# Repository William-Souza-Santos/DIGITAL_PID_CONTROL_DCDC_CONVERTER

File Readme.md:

# ⚡ FUZZY CONTROL APPLIED TO A BIDIRECTIONAL BUCK-BOOST DC-DC CONVERTER

This project presents the design and implementation of a four-switch bidirectional buck-boost DC-DC converter, featuring a fuzzy logic-based digital control system. The converter is designed for embedded and automotive power applications, ensuring stability, precision, and adaptability in bidirectional energy management.

---

## 🔍 Circuit Overview

---

## 🔧 Project Highlights

- Implementation of a non-linear fuzzy logic controller to dynamically regulate the converter's duty cycle.
- Simulations conducted in **MATLAB/Simulink** and **Proteus**, covering both open-loop and closed-loop control strategies.
- Embedded firmware developed for the **ATmega328P** microcontroller to enable real-time control.
- Complete **PCB design**, including schematic capture, PCB layout, and 3D visualization.

---

## 🎯 Objective

To design and validate a high-efficiency bidirectional DC-DC converter capable of operating in buck, boost, and buck-boost modes, maintaining stable output voltage under varying load and input conditions.

---

## 🚗 Motivation: Automotive and Beyond

The primary motivation for this project lies in the growing demand for reliable DC-DC power converters in **automotive systems**, where multiple ECUs operate at different voltage levels. A bidirectional buck-boost converter ensures safe and efficient energy flow between these modules and energy storage systems such as batteries or supercapacitors.

Although tailored for automotive use, the converter is also applicable to:

- 🔋 Battery Management Systems (BMS)  
- ☀️ Renewable Energy Systems  
- 🏭 Industrial Automation  
- ✈️ Aerospace Power Electronics  

---

## 🧪 Simulation: Circuit in Proteus

---

## 📝 Theoretical Foundations

<p align="center">
  <strong>Operating Modes</strong><br>
  <br>
</p>

<p align="center">
  <strong>BUCK</strong><br>
  <br>
</p>

<p align="center">
  <strong>BUCK-BOOST (Transition Mode)</strong><br>
  <br>
</p>

<p align="center">
  <strong>BOOST</strong><br>
  <br>
</p>

---

## 📝 Theoretical Foundations (Table Operating)

<p align="center">
  <strong>A-B OPERATING</strong><br>
  <br>
</p>

<p align="center">
  <strong>B-A OPERATING</strong><br>
  <br>
</p>

---

## 🔁 Bidirectional Operation (Open-Loop Tests)

<p align="center">
  <strong>A → B (Boost Mode)</strong><br>
  <br>
</p>

<p align="center">
  <strong>A → B (Buck Mode)</strong><br>
  <br>
</p>

<p align="center">
  <strong>B → A (Boost Mode)</strong><br>
  <br>
</p>

<p align="center">
  <strong>B → A (Buck Mode)</strong><br>
  <br>
</p>

<!--
## 📉 Theorical Fundamentation and Transition Mode

<p align="center">
  <strong>Buck Waveform</strong><br>
  <br>
</p>

<p align="center">
   <strong>Boost Waveform</strong><br>
  
</p>
-->

---
## 🖥️ Choosing a Microcontroller

<p align="center">
  <br>
</p>

---

## 🤖 Fuzzy Control System (Closed-Loop in Simulink)

<p align="center">
  <strong>Closed-Loop Control Model</strong><br>
  <br>
</p>

---

## 🧩 Schematic

<p align="center">
  <br>
</p>

---

## 🧱 3D PCB View

<p align="center">
  <br>
</p>

---

## 👨‍💻 Authors

- Marcelo Oliveira de Jesus Júnior  
- Victor Pereira dos Santos  
- William Souza Santos

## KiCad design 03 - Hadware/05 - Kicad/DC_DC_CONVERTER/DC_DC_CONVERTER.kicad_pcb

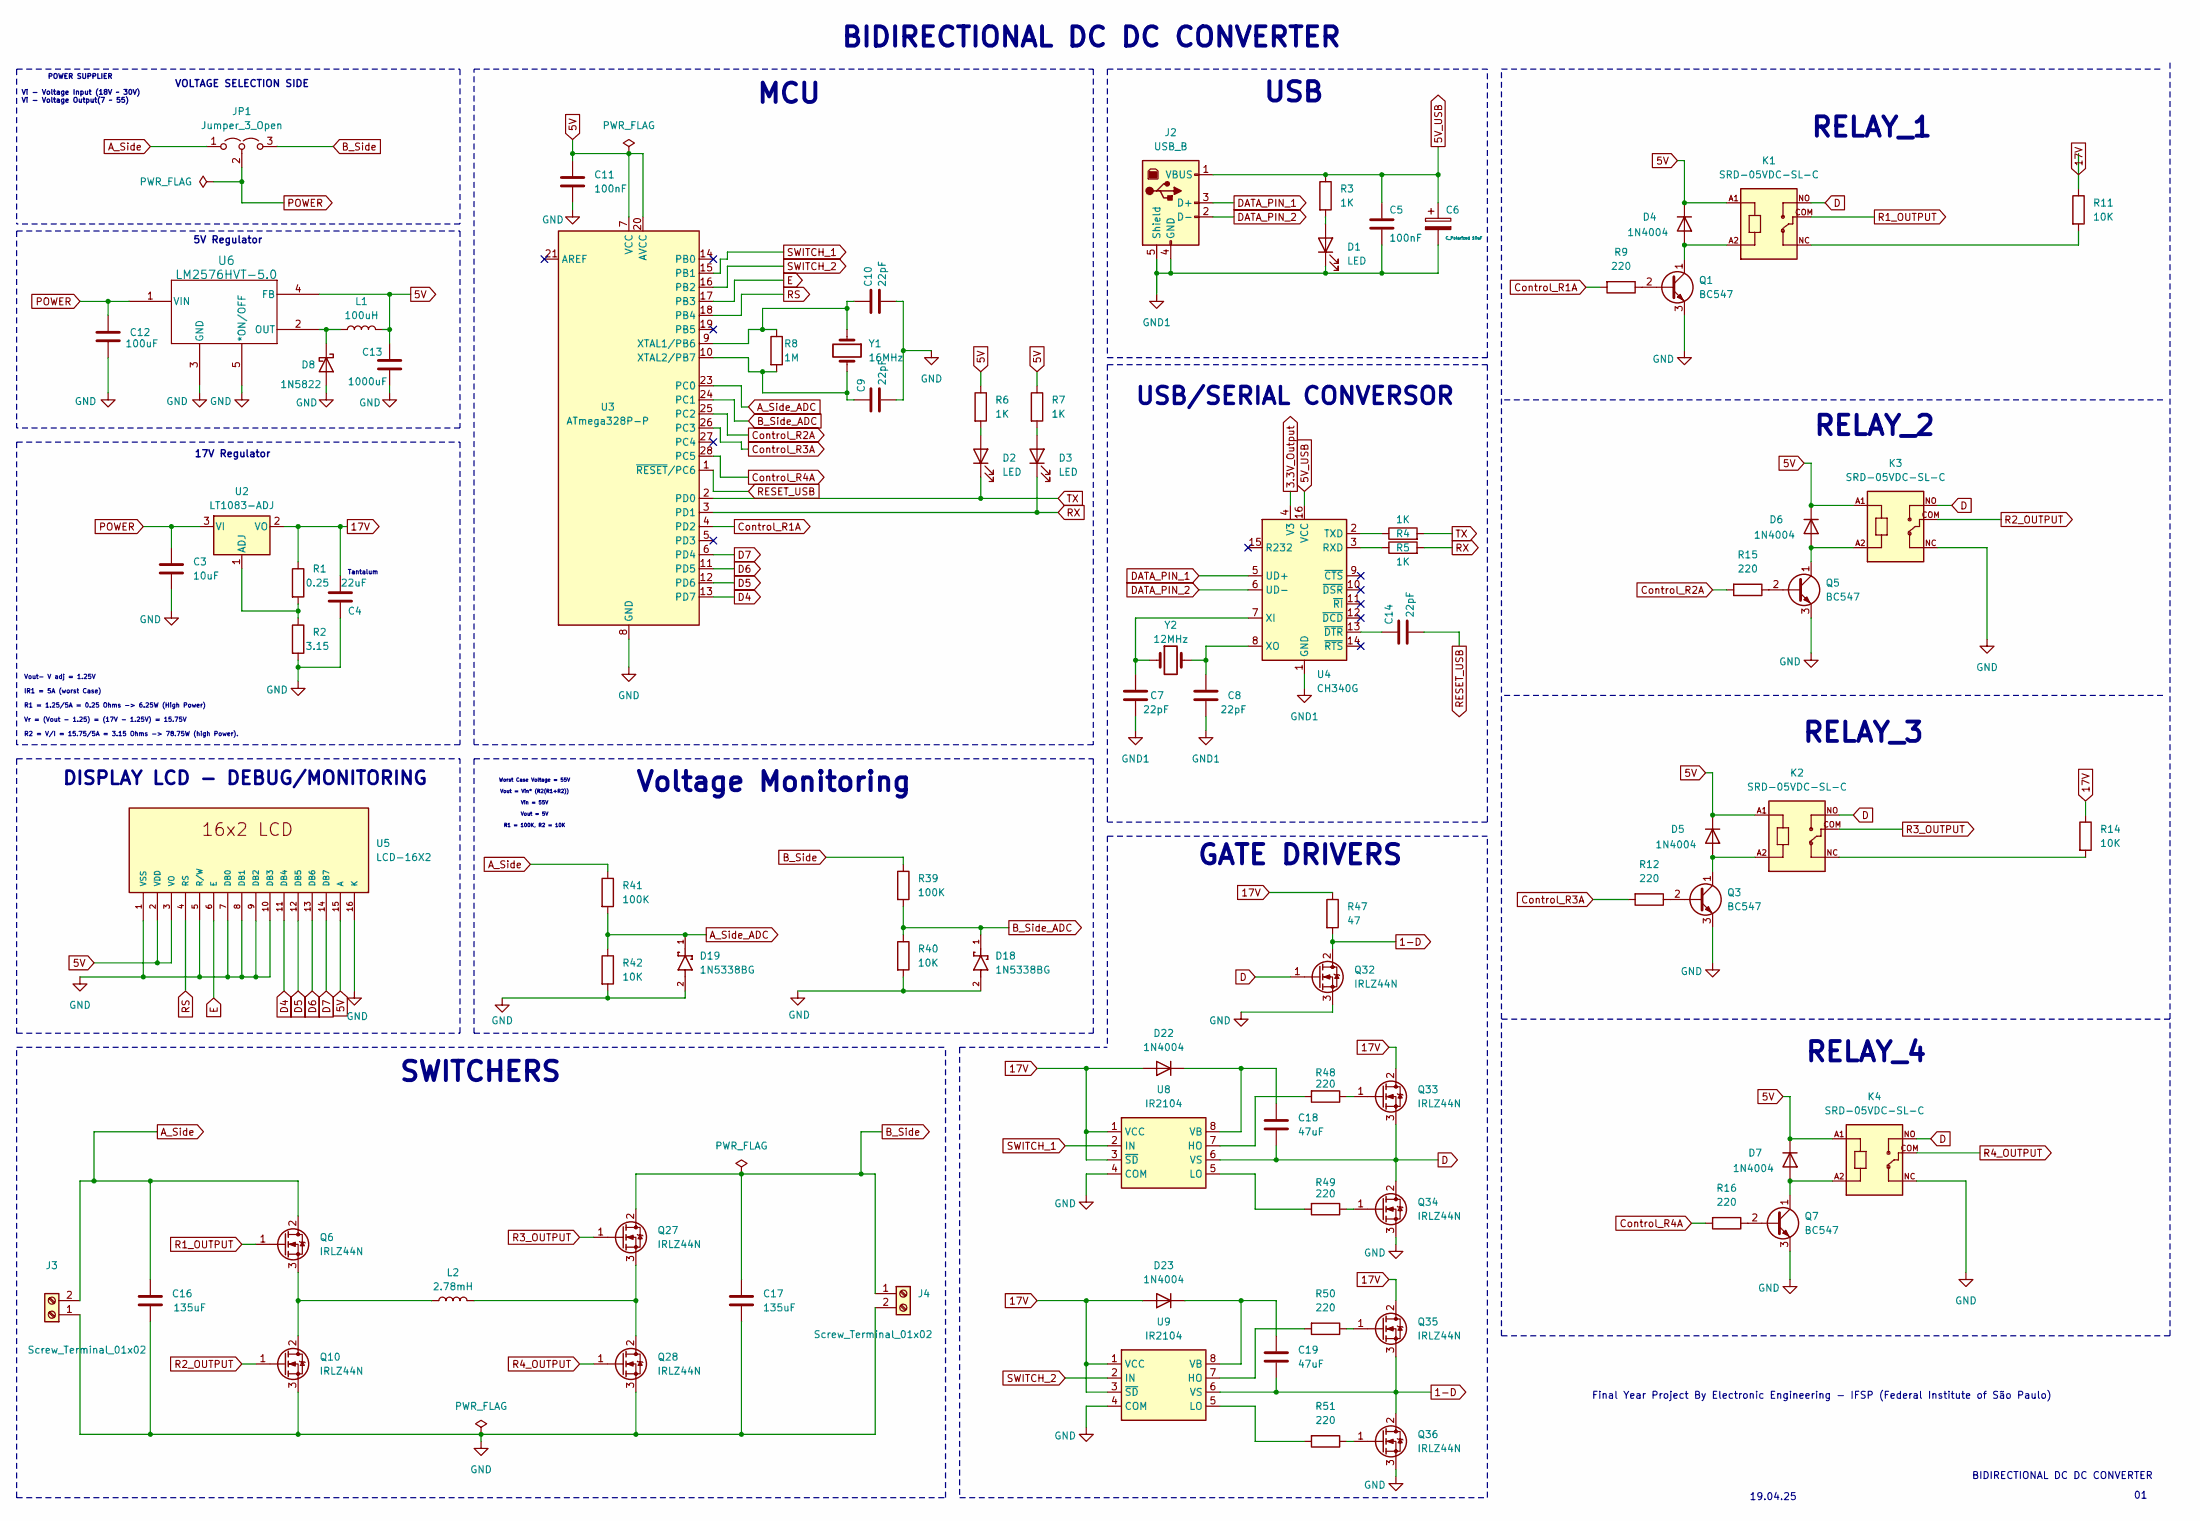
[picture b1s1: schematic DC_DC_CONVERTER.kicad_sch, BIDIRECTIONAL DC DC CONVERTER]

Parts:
C3: 10uF; CP_Radial_D8.0mm_P5.00mm
C4: 22uF; CP_Radial_D5.0mm_P2.50mm
C5, C11: 100nF; CP_Radial_D8.0mm_P5.00mm
C6: C_Polarized 10uF; CP_Radial_D8.0mm_P5.00mm
C7, C8, C9, C10, C14: 22pF; CP_Radial_D8.0mm_P5.00mm
C12: 100uF; CP_Radial_D8.0mm_P5.00mm
C13: 1000uF; CP_Radial_D8.0mm_P5.00mm
C16, C17: 135uF; CP_Radial_D8.0mm_P5.00mm
C18, C19: 47uF; CP_Radial_D8.0mm_P5.00mm
D1, D2, D3: LED; LED_D3.0mm
D4, D5, D6, D7, D22, D23: 1N4004; D_DO-41_SOD81_P10.16mm_Horizontal
D8: 1N5822; D_DO-201AD_P15.24mm_Horizontal
D18, D19: 1N5338BG; DIOAD1543W101L863D368; PARTREV O
J2: USB_B; USB_B_OST_USB-B1HSxx_Horizontal
J3, J4: Screw_Terminal_01x02; HANDSON_KF301-2P
JP1: Jumper_3_Open; PinHeader_1x03_P2.54mm_Vertical
K1, K2, K3, K4: SRD-05VDC-SL-C; RELAY_SRD-05VDC-SL-C
L1: 100uH; L_Radial_D12.0mm_P6.00mm_Murata_1900R
L2: 2.78mH; L_Radial_D12.0mm_P6.00mm_Murata_1900R
Q1, Q3, Q5, Q7: BC547; TO-92_Inline
Q6, Q10, Q27, Q28, Q32, Q33, Q34, Q35, Q36: IRLZ44N; TO-220-3_Vertical
R1: 0.25; R_Axial_DIN0414_L11.9mm_D4.5mm_P15.24mm_Horizontal
R2: 3.15; R_Axial_DIN0414_L11.9mm_D4.5mm_P15.24mm_Horizontal
R3, R4, R5, R6, R7: 1K; R_Axial_DIN0414_L11.9mm_D4.5mm_P15.24mm_Horizontal
R8: 1M; R_Axial_DIN0414_L11.9mm_D4.5mm_P15.24mm_Horizontal
R9, R12, R15, R16, R48, R49, R50, R51: 220; R_Axial_DIN0414_L11.9mm_D4.5mm_P15.24mm_Horizontal
R11, R14, R40, R42: 10K; R_Axial_DIN0414_L11.9mm_D4.5mm_P15.24mm_Horizontal
R39, R41: 100K; R_Axial_DIN0414_L11.9mm_D4.5mm_P15.24mm_Horizontal
R47: 47; R_Axial_DIN0414_L11.9mm_D4.5mm_P15.24mm_Horizontal
U2: LT1083-ADJ; TO-3P_P_LIT
U3: ATmega328P-P; DIP-28_W7.62mm
U4: CH340G; SOIC-16_3.9x9.9mm_P1.27mm
U5: LCD-16X2; MODULE_LCD-16X2; PARTREV N/A
U6: LM2576HVT-5.0; T05A_TEX
U8, U9: IR2104; DIP762W45P254L988H533Q8
Y1: 16MHz; Crystal_HC49-4H_Vertical
Y2: 12MHz; Crystal_HC49-4H_Vertical

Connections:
1-D: C19.2, Q32.2 (D), Q35.3 (S), Q36.2 (D), R47.2, U9.6 (VS)
3.3V_Output: U4.4 (V3)
5V: C11.1, C13.1, D4.1 (K), D5.1 (K), D6.1 (K), D7.1 (K), K1.A1, K2.A1, K3.A1, K4.A1, L1.2, R6.1, R7.1, U3.7 (VCC), U3.20 (AVCC), U5.2 (VDD), U5.3 (VO), U5.15 (A), U6.4 (FB)
5V_USB: C5.1, C6.1, J2.1 (VBUS), R3.1, U4.16 (VCC)
17V: C4.1, D22.2 (A), D23.2 (A), Q33.2 (D), Q35.2 (D), R1.1, R11.1, R14.1, R47.1, U2.2 (VO), U8.1 (VCC), U8.3 (~SD), U9.1 (VCC), U9.3 (~SD)
A_Side: C16.1, J3.2, JP1.1 (A), Q6.2 (D), R41.1
A_Side_ADC: D19.1, R41.2, R42.1, U3.23 (PC0)
B_Side: C17.1, J4.1, JP1.3 (B), Q27.2 (D), R39.1
B_Side_ADC: D18.1, R39.2, R40.1, U3.24 (PC1)
Control_R1A: R9.2, U3.4 (PD2)
Control_R1B: U3.5 (PD3); also elsewhere on the board
Control_R2A: R15.2, U3.25 (PC2)
Control_R3A: R12.2, U3.26 (PC3)
Control_R3B: U3.27 (PC4); also elsewhere on the board
Control_R4A: R16.2, U3.28 (PC5)
D: C18.2, K1.NO, K2.NO, K3.NO, K4.NO, Q32.1 (G), Q33.3 (S), Q34.2 (D), U8.6 (VS)
D4: U3.13 (PD7), U5.11 (DB4)
D5: U3.12 (PD6), U5.12 (DB5)
D6: U3.11 (PD5), U5.13 (DB6)
D7: U3.6 (PD4), U5.14 (DB7)
DATA_PIN_1: J2.3 (D+), U4.5 (UD+)
DATA_PIN_2: J2.2 (D-), U4.6 (UD-)
E: U3.17 (PB3), U5.6 (E)
GND: C3.2, C4.2, C9.2, C10.2, C11.2, C12.2, C13.2, C16.2, C17.2, D8.2 (A), D18.2, D19.2, J3.1, J4.2, K3.NC, K4.NC, Q1.3 (E), Q3.3 (E), Q5.3 (E), Q7.3 (E), Q10.3 (S), Q28.3 (S), Q32.3 (S), Q34.3 (S), Q36.3 (S), R2.2, R40.2, R42.2, U3.8 (GND), U3.22 (GND), U5.1 (VSS), U5.5 (R/W), U5.7 (DB0), U5.8 (DB1), U5.9 (DB2), U5.10 (DB3), U5.16 (K), U6.3 (GND), U6.5 (*ON/OFF), U8.4 (COM), U9.4 (COM); also elsewhere on the board
GND1: C5.2, C6.2, C7.2, C8.2, D1.1 (K), J2.4 (GND), J2.5 (Shield), U4.1 (GND)
unnamed: D1.2 (A), R3.2
unnamed: D2.2 (A), R6.2
unnamed: D3.2 (A), R7.2
unnamed: D4.2 (A), K1.A2, Q1.1 (C)
unnamed: D5.2 (A), K2.A2, Q3.1 (C)
unnamed: D6.2 (A), K3.A2, Q5.1 (C)
unnamed: D7.2 (A), K4.A2, Q7.1 (C)
unnamed: D8.1 (K), L1.1, U6.2 (OUT)
unnamed: C18.1, D22.1 (K), U8.8 (VB)
unnamed: C19.1, D23.1 (K), U9.8 (VB)
unnamed: Q1.2 (B), R9.1
unnamed 36: K1.NC, R11.2; also elsewhere on the board
unnamed: Q3.2 (B), R12.1
unnamed 39: K2.NC, R14.2; also elsewhere on the board
unnamed: Q5.2 (B), R15.1
unnamed: Q7.2 (B), R16.1
unnamed: L2.1, Q6.3 (S), Q10.2 (D)
unnamed: L2.2, Q27.3 (S), Q28.2 (D)
unnamed: Q33.1 (G), R48.1
unnamed: Q34.1 (G), R49.1
unnamed: Q35.1 (G), R50.1
unnamed: Q36.1 (G), R51.1
unnamed: R1.2, R2.1, U2.1 (ADJ)
unnamed: C10.1, R8.1, U3.9 (XTAL1/PB6), Y1.1
unnamed: C9.1, R8.2, U3.10 (XTAL2/PB7), Y1.2
unnamed: R5.1, U4.3 (RXD)
unnamed: R4.1, U4.2 (TXD)
unnamed: C7.1, U4.7 (XI), Y2.1
unnamed: C8.1, U4.8 (XO), Y2.2
unnamed: C14.1, U4.13 (~DTR)
unnamed: R48.2, U8.7 (HO)
unnamed: R49.2, U8.5 (LO)
unnamed: R50.2, U9.7 (HO)
unnamed: R51.2, U9.5 (LO)
POWER: C3.1, C12.1, JP1.2 (C), U2.3 (VI), U6.1 (VIN)
R1_OUTPUT: K1.COM, Q6.1 (G)
R2_OUTPUT: K3.COM, Q10.1 (G)
R3_OUTPUT: K2.COM, Q27.1 (G)
R4_OUTPUT: K4.COM, Q28.1 (G)
RESET_USB: C14.2, U3.1 (~RESET/PC6)
RS: U3.18 (PB4), U5.4 (RS)
RX: D3.1 (K), R5.2, U3.3 (PD1)
SWITCH_1: U3.15 (PB1), U8.2 (IN)
SWITCH_2: U3.16 (PB2), U9.2 (IN)
TX: D2.1 (K), R4.2, U3.2 (PD0)

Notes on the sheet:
17V Regulator
Final Year Project By Electronic Engineering - IFSP (Federal Institute of São Paulo)
DISPLAY LCD - DEBUG/MONITORING
19.04.25
MCU
Tantalum
Worst Case Voltage = 55V Vout = Vin* (R2(R1+R2)) Vin = 55V Vout = 5V R1 = 100K, R2 = 10K
VOLTAGE SELECTION SIDE
RELAY_4
POWER SUPPLIER Vi - Voltage Input (18V ~ 30V) Vi - Voltage Output(7 ~ 55)
BIDIRECTIONAL DC DC CONVERTER
USB/SERIAL CONVERSOR
SWITCHERS
Voltage Monitoring
5V Regulator
BIDIRECTIONAL DC DC CONVERTER
RELAY_3
RELAY_1
Vout- V adj = 1.25V IR1 = 5A (worst Case) R1 = 1.25/5A = 0.25 Ohms -> 6.25W (High Power) Vr = (Vout - 1.25) = (17V - 1.25V) = 15.75V R2 = V/I = 15.75/5A = 3.15 Ohms -> 78.75W (high Power).
USB
RELAY_2
GATE DRIVERS

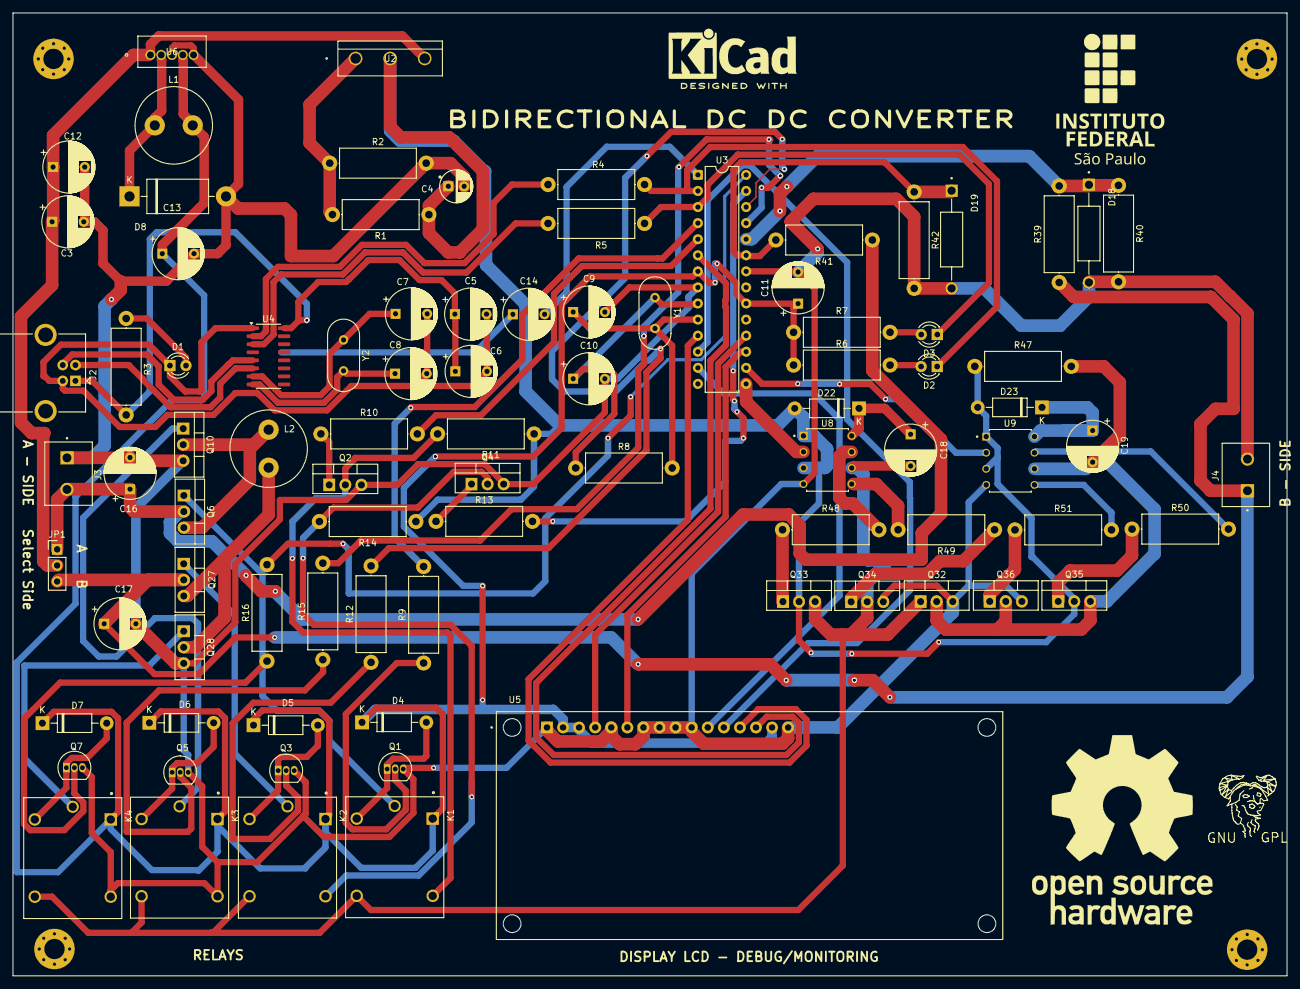
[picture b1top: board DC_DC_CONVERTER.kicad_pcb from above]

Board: 2 copper layers, 201.3 x 152.1 mm, 87 parts (0 on the bottom side), 71 nets.

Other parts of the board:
Q2, Q4: IRLZ44N; TO-220-3_Vertical
R10, R13: 220; R_Axial_DIN0414_L11.9mm_D4.5mm_P15.24mm_Horizontal

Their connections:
Control_R1B: R10.2; also elsewhere on the board
Control_R3B: R13.2; also elsewhere on the board
GND: Q2.3 (S), Q4.3 (S); also elsewhere on the board
unnamed 36: Q2.2 (D); also elsewhere on the board
unnamed: Q2.1 (G), R10.1
unnamed 39: Q4.2 (D); also elsewhere on the board
unnamed: Q4.1 (G), R13.1

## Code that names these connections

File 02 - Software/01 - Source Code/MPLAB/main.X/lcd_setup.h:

//--------------------------------------------------------------
void lcd_setup(){
	// Define pins as output
	DDRD |= (1<<PD2) | (1<<PD3);		// E (D2), RS (D3)
	DDRD |= (1<<PD4) | (1<<PD5) | (1<<PD6) | (1<<PD7);	// Data path
	
	// Initializes the LCD
	inic_LCD_4bits();				// From "LCD.h" header
	cmd_LCD(0x01,0);				// Clear the LCD
}
//--------------------------------------------------------------
void lcd_sub(){
	char buffer[6] = "";
	
	sprintf(buffer, "%.1f", ref);
	cmd_LCD(0x80,0);
	escreve_LCD(buffer);
	
	sprintf(buffer, "%.1f", source);
	cmd_LCD(0x85,0);
	escreve_LCD(buffer);
	
	cmd_LCD(0x8A,0);
	if(!b)escreve_LCD("-");
	else if(a)escreve_LCD("+");
	else escreve_LCD("*");
	
	sprintf(buffer, "%.1f", output);
    cmd_LCD(0x8C,0);
	escreve_LCD(buffer);
	
	sprintf(buffer, "%.1f", error);
    cmd_LCD(0xC0,0);
	escreve_LCD(buffer);
	
	sprintf(buffer, "%.2f", fis_duty);
    cmd_LCD(0xC5,0);
	escreve_LCD(buffer);
	
	sprintf(buffer, "%.2f", duty);
    cmd_LCD(0xCB,0);
	escreve_LCD(buffer);
}
//--------------------------------------------------------------

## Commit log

2025-01-06 Commit inicial
2025-01-06 Segundo commit
2025-01-06 Fix the title
2025-01-06 Add Button
2025-01-06 Add Folders
    This commit is responsible to add new folder in this project
2025-01-07 Update Readme.md
    Update readme.me
2025-01-07 Subir monografia mais recente github NmBcGUBy
2025-01-08 utlima modificação
2025-01-08 the last modification
2025-01-08 Criação da pasta Matlab
2025-01-08 update readme.me testar git extension
2025-01-08 Add Proteus Simulation
2025-01-08 Adding TCC proposal to the Requirements folder
2025-01-09 the last commit of the day
2025-01-09 Teste vinculãção de contas
2025-01-09 update readme via git bash
2025-01-09 add ltspice simulation folder
2025-01-09 Teste movimentação git status profile
2025-01-10 teste Victor
2025-01-10 update source monografia
2025-01-14 Update source monograph
2025-01-26 add topology and classification of DC DC converters in monograph 26.01.25
2025-01-31 added deep fundation about choopers in monograph 30.01.25
2025-02-07 Udpate monograph 06.02.25
2025-02-10 Create Proteus and LTSpice Simulation
2025-02-13 Add arduino in proteus simulation
2025-02-15 add gate driver circuit in proteus
2025-02-15 add display lcd in proteus simulation
2025-02-21 Add abstract in monograph 21.02.25
2025-02-21 Add Hardware Requirements 21.02.25
2025-02-22 add firmware to proteus simulation 21.02.25
2025-02-23 Add lista de abreviatures 23.02.25
2025-03-02 Add RTOS File
2025-03-02 Add labview libraries
2025-03-02 Moved the folder labview arduino
2025-03-03 RTOS + LabVIEW run together 3.3.25
2025-03-05 add bidirectional circuit in conversor 04.03.25
2025-03-06 Replaced IRF540N Mosfet with IRLZ44N Mosfet - Less Rds(on) 05.03.25
2025-03-06 Replaced inductor 22uH with inductor 47uH 05.03.25
2025-03-07 Upate title of monograph add Four Switch 06.03.25
2025-03-16 Add duty cycle view in the display
2025-03-17 Monograph Rev 0.1 17.03.25
2025-04-07 Proteus simulation semi_final_version 06.04.25
2025-04-11 Proteus Simulation Final Version 10.04.25
2025-04-12 Final simulation version proteus 12.04.25
2025-04-12 replace IRF540N by IRLZ44N in gate driver circuit 12.04.25
2025-04-18 update the repository
2025-04-18 add manufacturing folder
2025-04-18 content inside the manufactring folder
2025-04-18 adjust proteus simulation
2025-04-18 update proteus simulation check
2025-04-19 update design calculations
2025-04-19 update folder org
2025-05-04 Schematic final version 04.05.25
2025-05-18 release pires 18.05.25 update: Schematic/Layout/Priteus simulation/Matlab Simulation/Monogroph
2025-07-06 add picture folder
2025-07-06 add circuit picture
2025-07-06 Update Readme.md with pictures
2025-07-06 adding pictures in the folder
2025-07-06 adding pictures related to operation
2025-07-06 add buck boost picture switches
2025-07-06 Adding final monograph 06.07.25
2025-07-08 Source code, MATLAB, Proteus (Victor)
